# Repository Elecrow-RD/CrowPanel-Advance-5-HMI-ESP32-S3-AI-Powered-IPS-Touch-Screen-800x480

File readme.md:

## Menu
### 1, Product picture
### 2, Product version number
### 3, product information
### 4, Use the driver module
### 5,Quick Start
### 6,Folder structure.
### 7,Pin definition
### 8,Guidelines for downloading some of the files from the github repository

### 1, Product picture

### 2, Product version number

|      | Hardware | Software | Remark |
| ---- | -------- | -------- | ------ |
| 1    | V1.0     | V1.0     | old |
| 2    | V1.1     | V1.1     | old |
| 3    | V1.2     | V1.2     | old |
| 4    | V1.3     | V1.2     | latest |

### Version update points:

① **Version 1.1** updated the control of backlight on the basis of the original, the backlight of version 1.1 is controlled by STC8H1K28 microcontroller, and the backlight is lit in the program by sending the value to this microcontroller address (0x30). The values are 0x05, 0x06, 0x07, 0x08, 0x09 and 0x10, where 0x05 switches off the backlight and 0x10 is the maximum brightness.

The control of the buzzer is similar to that of the backlight: sending 0x15 activates the buzzer, while sending 0x16 deactivates it.

The speaker is controlled in the same manner: sending 0x17 activates the speaker, while sending 0x18 deactivates it.

② **Version 1.1** has a new option for function switching, see above for details. When using the case, please select the corresponding program to test or modify according to the version number of your motherboard.

③ **Version 1.2** introduces an updated backlight control function. In this iteration, the backlight is managed by the STC8H1K28 microcontroller. The programme illuminates the backlight by transmitting numerical values to the microcontroller's address (0x30). Brightness adjustment spans 0-245 levels, where 0 denotes maximum brightness, 244 represents minimum brightness, and 245 disables the backlight.
Updated the button module.
The buzzer control principle mirrors that of the backlight: sending 246 activates the buzzer, while sending 247 deactivates it.

④ **Version 1.2** ,Only the button component has been updated. All other hardware and I/O pins remain the same as in the previous version.

⑤ **Version 1.3** is simply an update to the previous version that modifies the packaging of the touchscreen FPC connector. There are no other differences.

### 3, product information

| Main Chip-ESP32-S3-WROOM-1-N16R8         |                                                              |
| -------------------------------------------- | ------------------------------------------------------------ |
| CPU/SoC                                      | high-performance Xtensa 32-bit LX7 dual-core processor, with up to 240MHz |
| System Memory                                | 512KB SRAM、8M PSRAM                                         |
| Memory                                       | 16M Flash，384KB ROM                                         |
| Development Language                         | MicroPython、C/C++                                           |
| Development Environment                      | ESP-IDF、Arduino IDE、PlatformIO、MicroPython        |
| **Screen**                                   |                                                              |
| Size                                         | 5.0 inch                                                     |
| Diver IC                                     | ST7262                                                       |
| Resolution                                   | 800*480                                                      |
| Display Panel                                | IPS Panel                                                    |
| Touch Panel                                  | Capacitive Single Touch                                      |
| Viewing Angle                                | 178°                                                         |
| Brightness                                   | 400 cd/m²(Typ.)                                              |
| Color Depth                                  | 16-bit                                                       |
| **Wireless Communication - Onboard Antenna** |                                                              |
| WiFi                                         | Support 2.4GHz, 802.11a/b/g/n                                |
| Bluetooth                                    | Support Bluetooth 5.0 and BLE                                |
| Other                                        | **Zigbee、LoRa、nRF2401、Matter、Thread and Wi-Fi 6 (Optional)** |
| **Interface/Function**                       |                                                              |
| Interface                                    | USB port, UART, I2C, SD card slot, battery socket, speaker port, microphone, etc. |
| Function                                     | RTC clock, audio amplifier, volume control, battery charge management, USB to UART, etc. |
| **Button/LED Indicator**                     |                                                              |
| Reset Button                                 | Yes, press to reset device                                   |
| Boot Button                                  | Yes, press and hold the power button to burn the program     |
| PWR                                          | Power indicator                                              |
| CHG                                          | Lithium battery charging status, completion indication       |
| **Other**                                    |                                                              |
| Installation method                          | Back hanging, fixed hole                                     |
| Operating temperature                        | -20~70 °C                                                    |
| Storage temperature                          | -30~80 °C                                                    |
| Power Input                                  | 5V/2A, USB or UART terminal                                  |
| Active Area                                  | 108mm*65mm                                                   |
| Dimensions                                   | 136.4\*84.7*15.4mm                                            |

### 4, Use the driver module

| Name   | dependency library                      |
| ------ | --------------------------------------- |
| LVGL   | lvgl/lvgl@8.3.3                         |
| ST7789 | Adafruit GFX Library<br/>version=1.11.0 |

### 5,Quick Start
### Arduino IDE starts

#### Teaching Case Path：./example/example_code5.0

1.Download the library files used by this product to the 'libraries' folder.

C:\Users\Documents\Arduino\libraries\

2.Open the Arduino IDE

3.Open the code configuration environment and burn it

### ESP-IDF starts

#### Teaching Case Path：./example/idf_code

1.Right-click on an empty space in the project folder and select "Open with VS Code" to open the project.

2.In the IDF plug-in, select the port, then compile and flash

### 6,Folder structure.

|--3D file： Contains 3D model files (.stp) for the hardware. These files can be used for visualization, enclosure design, or integration into CAD software.

|--Datasheet: Includes datasheets for components used in the project, providing detailed specifications, electrical characteristics, and pin configurations.

|--Eagle_SCH&PCB: Contains **Eagle CAD** schematic (`.sch`) and PCB layout (`.brd`) files. These are used for circuit design and PCB manufacturing.

|--example: Provides example code and projects to demonstrate how to use the hardware and libraries. These examples help users get started quickly.

|--factory_firmware: Stores pre-compiled factory firmware that can be directly flashed onto the device. This ensures the device runs the default functionality.

|--factory_sourcecode:  Contains the source code for the factory firmware, allowing users to modify and rebuild the firmware as needed.

|--libraries: Includes necessary libraries required for compiling and running the project. These libraries provide drivers and additional functionalities for the hardware.

|--Squareline_studio Instructions for use: Squareline_studio instructions: Demonstrate the use of squareline studio.

### 7,Pin definition

#define HSPI_MISO  4

#define HSPI_MOSI  6

#define HSPI_SCLK  5

#define HSPI_SS    19

#define SD_MOSI 6

#define SD_MISO 4
#define SD_SCK 5

#define SD_CS 0 //The chip selector pin is not connected to IO

#define I2S_DOUT 4

#define I2S_BCLK 5

#define I2S_LRC 6

​      cfg.pin_d0 = GPIO_NUM_21;    // B0

​      cfg.pin_d1 = GPIO_NUM_47;    // B1

​      cfg.pin_d2 = GPIO_NUM_48;   // B2

​      cfg.pin_d3 = GPIO_NUM_45;    // B3

​      cfg.pin_d4 = GPIO_NUM_38;    // B4

​      cfg.pin_d5 = GPIO_NUM_9;    // G0

​      cfg.pin_d6 = GPIO_NUM_10;    // G1

​      cfg.pin_d7 = GPIO_NUM_11;    // G2

​      cfg.pin_d8 = GPIO_NUM_12;   // G3

​      cfg.pin_d9 = GPIO_NUM_13;   // G4

​      cfg.pin_d10 = GPIO_NUM_14;   // G5

​      cfg.pin_d11 = GPIO_NUM_7;  // R0

​      cfg.pin_d12 = GPIO_NUM_17;  // R1

​      cfg.pin_d13 = GPIO_NUM_18;  // R2

​      cfg.pin_d14 = GPIO_NUM_3;  // R3

​      cfg.pin_d15 = GPIO_NUM_46;  // R4

      cfg.pin_henable = GPIO_NUM_42;
      
      cfg.pin_vsync = GPIO_NUM_41;
      
      cfg.pin_hsync = GPIO_NUM_40;
      
      cfg.pin_pclk = GPIO_NUM_39;

​     cfg.pin_sda = GPIO_NUM_15;

​      cfg.pin_scl = GPIO_NUM_16;

### 8,Guidelines for downloading some of the files from the github repository

##### 1, open the link in your browser: https://downgit.github.io/

##### 2, paste the URL of the GitHub destination folder in the input box (example format: `https://github.com/username/repository name/tree/branch name/folder path`)

##### 3, even a that way to download the file.

①Click the “Create Download Link” button to create a download link, copy the link and open it with your browser to download the contents of the corresponding folder directly.

②Click Download, and you can also download it directly.

#### Note: DownGit downloads are stored by default in **your browser's default downloads folder**, usually:

- **Windows**: `C:\Users\your username\Downloads\` (downloads folder)
- **macOS**: `~/Downloads/` (downloads folder)
- **Linux**: `~/Downloads/` (Downloads folder)

If you change the default download path in your browser, the file will be stored in the download location you set. You can find the downloaded file path in your browser's **Download History** (shortcut `Ctrl + J` or `Cmd + J`).

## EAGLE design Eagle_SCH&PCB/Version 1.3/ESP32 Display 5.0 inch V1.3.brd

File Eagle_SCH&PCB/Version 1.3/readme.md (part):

# 5.0-Inch ESP32-S3 Hardware Driver Guide

| Item | Details |
|---|---|
| Document Version | V1.0 |
| Applicable Hardware | ESP32 Display 5.0 inch V1.3 |
| Baseline Date | 2026-07-30 |
| Author | OpenAI Codex (compiled through cross-referencing project materials) |
| Purpose | Hardware maintenance, driver porting, production testing, and onboarding handoff |

## 1. Document Scope and Determination Criteria

This document is based on cross-verification of the following project materials:

1. `Version 1.3/ESP32 Display 5.0 inch V1.3.sch`: EAGLE 9.6.2 schematic source file, used as the primary hardware evidence for components and net connections.
2. `Version 1.3/ESP32 Display 5.0 inch V1.3.brd`: PCB netlist, used to verify schematic nets and component pad connections.
3. `Version 1.3/ESP32 Display 5.0 inch V1.3.pdf`: Single-page schematic, used for visual verification of functional sections, interface names, and component models.
4. Board-level examples under `Arduino/`: Used as the project’s verified driver baseline, primarily covering display/touch, TF card, I2S audio, DHT20, nRF24L01, SX1262 LoRaWAN, and UART/Zigbee examples.

Conflicts are resolved according to the following priority:

> Working code configurations in successfully tested examples > actual PCB nets > schematic nets/labels > comments and filenames.

However, obvious placeholder values, conflicting comments, or parameters that do not correspond to actual electrical connections in the code are not automatically treated as reliable hardware facts. Such items are identified separately as risks in this document.

### 1.1 Evidence Levels

| Level | Meaning |
|---|---|
| A | The schematic/PCB matches the project driver code, and the code performs actual initialization or read/write operations |
| B | The schematic/PCB has been confirmed, but the project has no corresponding ESP32 driver, or the function is managed only by the onboard control MCU |
| C | The project provides a driver example, but it targets an optional module connected through an interface rather than a permanently mounted motherboard component |
| D | Only the presence of hardware or reserved signals can be confirmed; key protocols or parameters are missing and must be tested before porting |

No build logs, test reports, or test result files were found in the repository. Therefore, “verified code” in this document refers specifically to the product example baseline provided by the repository and does not mean that all tests were rerun on physical hardware for this review.

## 2. Product Hardware Architecture

The main controller is an ESP32-S3-WROOM-1-N16R8. The display uses an 800 × 480 RGB565 parallel interface. The GT911, onboard STC8H1K28 control MCU, RTC, and external I2C interface share GPIO15/16. GPIO4/5/6 and GPIO19/20 are multiplexed among the TF card, I2S, digital microphone, and wireless expansion interface through two CH486F analog switches and DIP-switch selection.

The onboard STC8H1K28 is an important auxiliary controller. It connects to touch reset, LCD backlight enable/power, the buzzer, charging status indicators, and ESP32_EN, and provides a board-control command interface to the ESP32 at I2C address `0x30`. Do not mistake these functions for direct ESP32 GPIO control.

## 3. Peripheral Overview

| Category | Component/Function | Primary Interface | ESP32 Resources | Onboard/External | Evidence |
|---|---|---|---|---|---|
| MCU | ESP32-S3-WROOM-1-N16R8 | Main controller | All board-level resources | Onboard | A |
| Auxiliary MCU | STC8H1K28-36I-LQFP32 | I2C board control | SDA15, SCL16; recovery pin GPIO1 indirectly associated with TP_INT | Onboard | A/B |
| Display | 5.0-inch 800×480 IPS RGB display | RGB565 parallel interface | GPIO3/7/9-14/17/18/21/38/45-48, 39-42 | Onboard | A |
| Touch | GT911 capacitive touch | I2C | SDA15, SCL16, INT GPIO1; RST controlled by STC | Onboard | A |
| Storage | MicroSD/TF card | SPI | MISO4, SCK5, MOSI6; see risk notes for CS | Onboard | A/discrepancy |
| RTC | PCF8563-compatible device | I2C | SDA15, SCL16, 32.768 kHz crystal, CR1220 backup | Onboard | B |
| Audio Output | NS4168 amplifier + speaker interface | I2S | DOUT4, BCLK5, LRCLK6; amplifier enabled by STC command | Onboard | A |
| Audio Input | LMD3526B261 digital MEMS microphone | I2S/PDM-type digital interface | CLK19, DATA20 | Onboard | B |
| Buzzer | BEEP_5025 passive buzzer | STC GPIO/PWM | No direct ESP32 connection; STC `P2.7/BEEP` | Onboard | B |
| Temperature and Humidity | DHT20 | I2C | SDA15, SCL16 | External | C |
| 2.4 GHz | nRF24L01 | SPI + CE | MISO4, SCK5, MOSI6, CSN19, CE20 | External | C |
| LoRa | SX1262 | SPI + DIO/RESET/BUSY | MISO4, SCK5, MOSI6, NSS8, DIO1 20, RESET19, BUSY2 | External | C |
| Zigbee/Serial Module | Model not specified | UART | RX19, TX20, 115200 8N1 | External | C/D |
| USB-to-Serial | CH340K | USB 2.0/UART0 | ESP_TXD0/ESP_RXD0, automatic download circuit | Onboard | B |
| Native USB | USB-C D+/D- | USB 2.0 | ESP32-S3 native USB fixed pins (nets routed through resistors) | Onboard | B |
| Power Input | USB-C 5 V, external 5 V/VIN | Power | Not GPIO | Onboard | B |
| Battery Charging | TP4059 + CR1220 RTC backup battery interface | Analog power/status | Status monitored by STC | Onboard | B |
| Main-Power DC/DC | RY3420/HM3416H | Step-down conversion | Not GPIO | Onboard | B |
| LCD Backlight | MT9201 | Boost constant-current + STC control | Indirectly controlled by ESP32 through I2C `0x30` | Onboard | A |
| Power/Charging LEDs | Red/green LEDs | STC GPIO | No direct ESP32 connection | Onboard | B |
| Buttons | BOOT, RESET | GPIO0, ESP32_EN | Active low | Onboard | B |
| DIP Switch | K1/DSHP02TS-S | Multiplexing selection | SEL0, SEL1, hardware configuration | Onboard | A/B |
| Expansion Interfaces | UART, I2C, GPIO, I2S/wireless headers | Multiple protocols | GPIO2/4/5/6/8/15/16/19/20, etc. | Onboard connectors | B/C |

## 4. ESP32-S3 GPIO Summary

| GPIO | Actual Project Function | Direction/Electrical Mode | Multiplexing and Restrictions |
|---:|---|---|---|
| 0 | BOOT; CS parameter passed by the SD example | Boot strapping pin, button active low | Peripherals should not pull it low during reset; see 6.4 regarding the validity of SD_CS |
| 1 | `IO1_TP_INT`, touch-interrupt net; examples use a low pulse to recover board control/touch | Normally input; open-drain-equivalent operation during fault recovery: output low for 120 ms, then return to input | Must not be continuously driven high in push-pull mode; code does not enable GT911 interrupt polling |
| 2 | Wireless expansion CS; SX1262 BUSY | Digital I/O | LoRa example uses it for BUSY; associated with J11 expansion functions |
| 3 | LCD R6 net, corresponding to one RGB565 red data bit | High-speed push-pull output | Dedicated to LCD |
| 4 | SPI MISO / I2S DOUT / wireless MISO | Input or push-pull output, depending on mode | Multiplexed through CH486F; functions are mutually exclusive |
| 5 | SPI SCK / I2S BCLK / wireless SCK | Push-pull clock output | Multiplexed through CH486F; functions are mutually exclusive |
| 6 | SPI MOSI / I2S LRCLK / wireless MOSI | Push-pull output | Multiplexed through CH486F; functions are mutually exclusive |
| 7 | LCD R3 | High-speed push-pull output | Dedicated to LCD |
| 8 | Wireless BUSY/expansion; SX1262 NSS | Digital I/O | LoRa code uses it as a push-pull chip select; verify DIP-switch and connector settings |
| 9-14 | LCD G2-G7 | High-speed push-pull output | Dedicated to LCD |
| 15 | I2C SDA | Bidirectional open-drain, with onboard 4.7 kΩ pull-up to 3.3 V | Shared by GT911, STC, RTC, and external I2C |
| 16 | I2C SCL | Open-drain clock, with onboard 4.7 kΩ pull-up to 3.3 V | Same as above |
| 17, 18 | LCD R4, R5 | High-speed push-pull output | Dedicated to LCD |
| 19 | nRF24 CSN / SX1262 RESET / UART RX / MIC CLK / LED example | Input or output, depending on use case | Multiplexed through CH486F; multiple examples cannot run simultaneously |
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
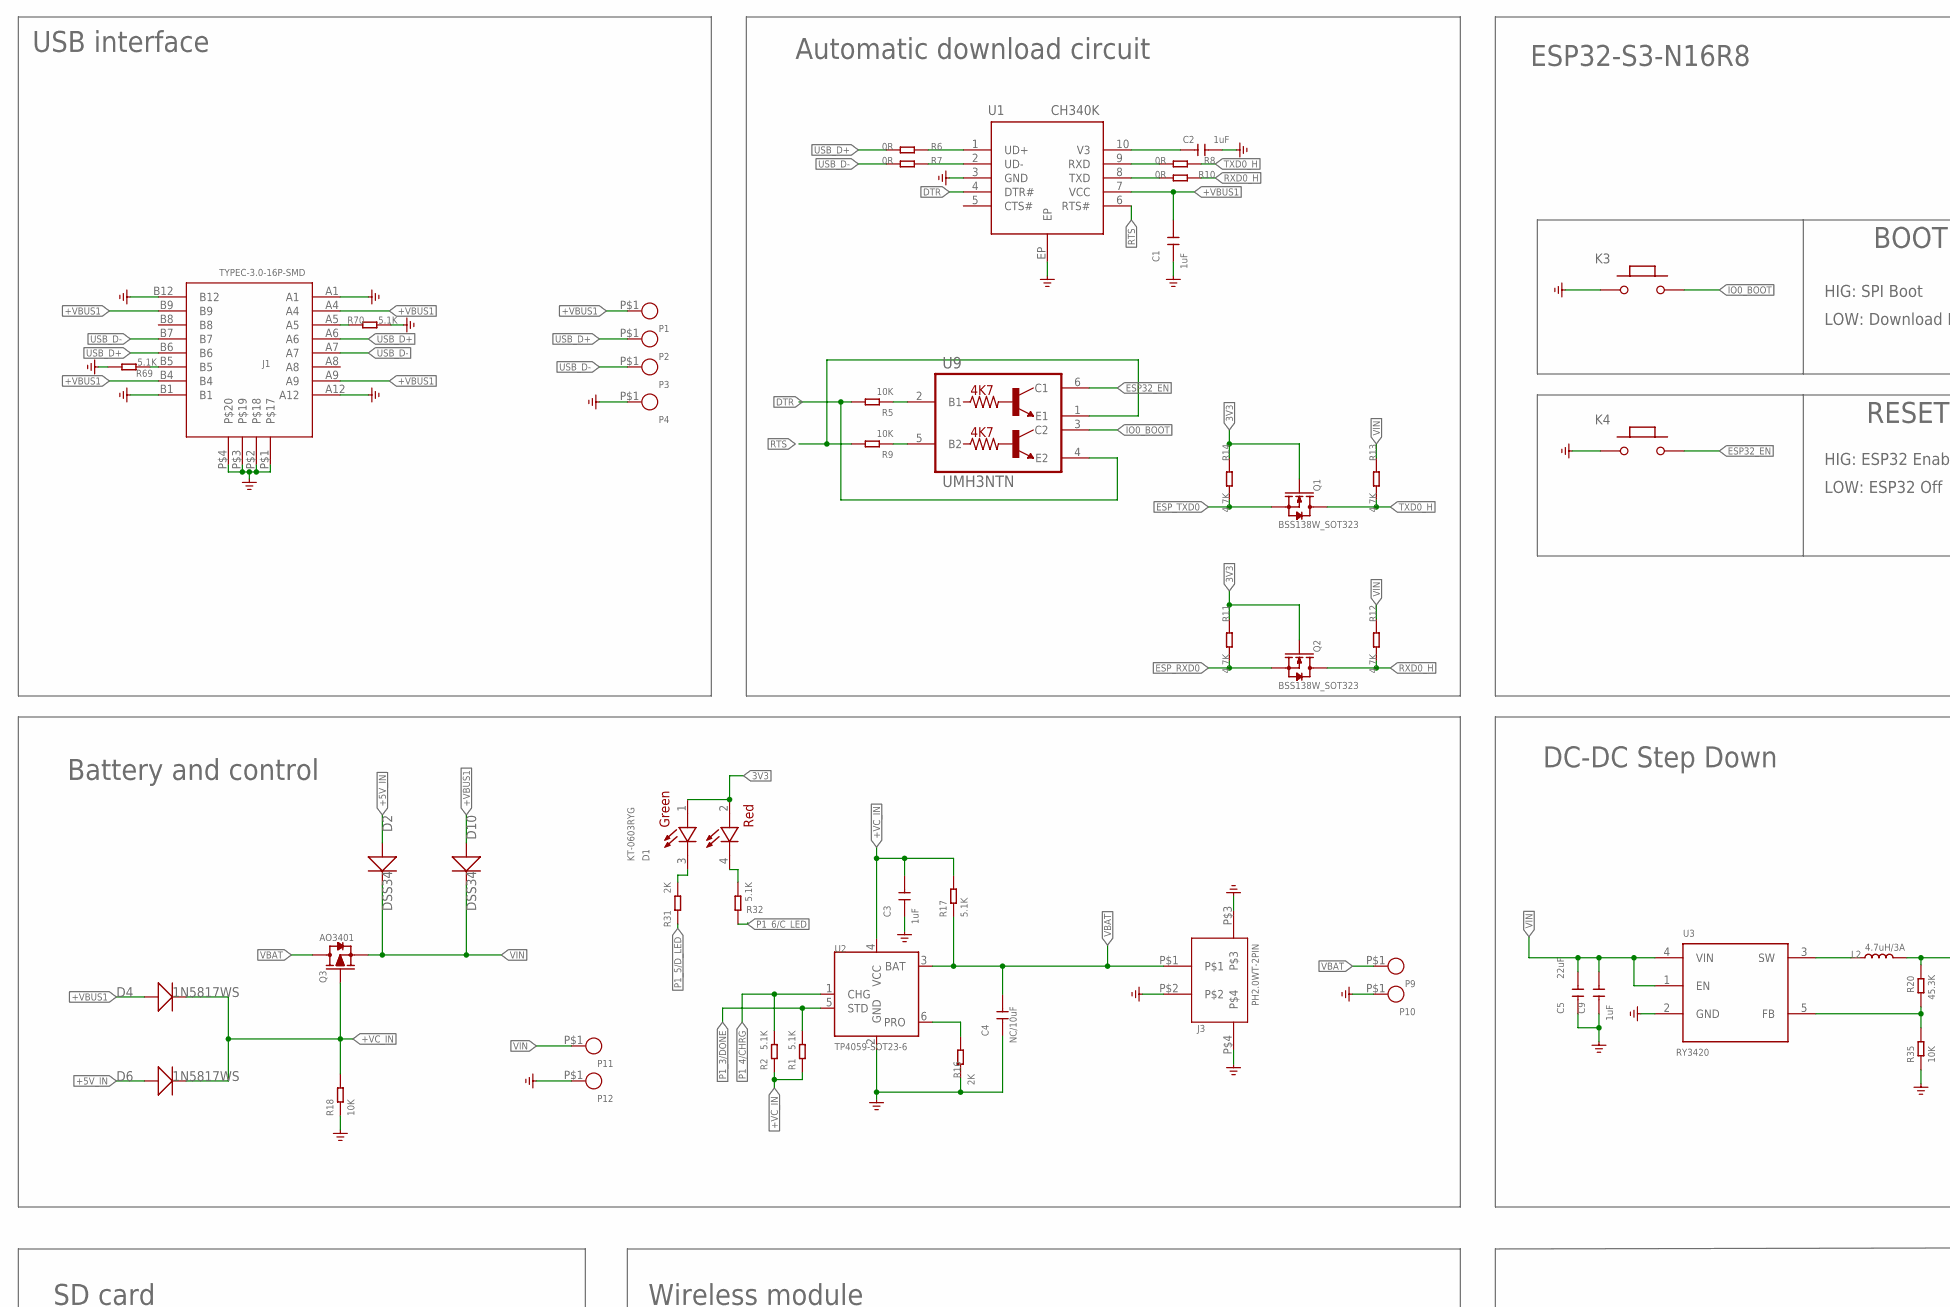
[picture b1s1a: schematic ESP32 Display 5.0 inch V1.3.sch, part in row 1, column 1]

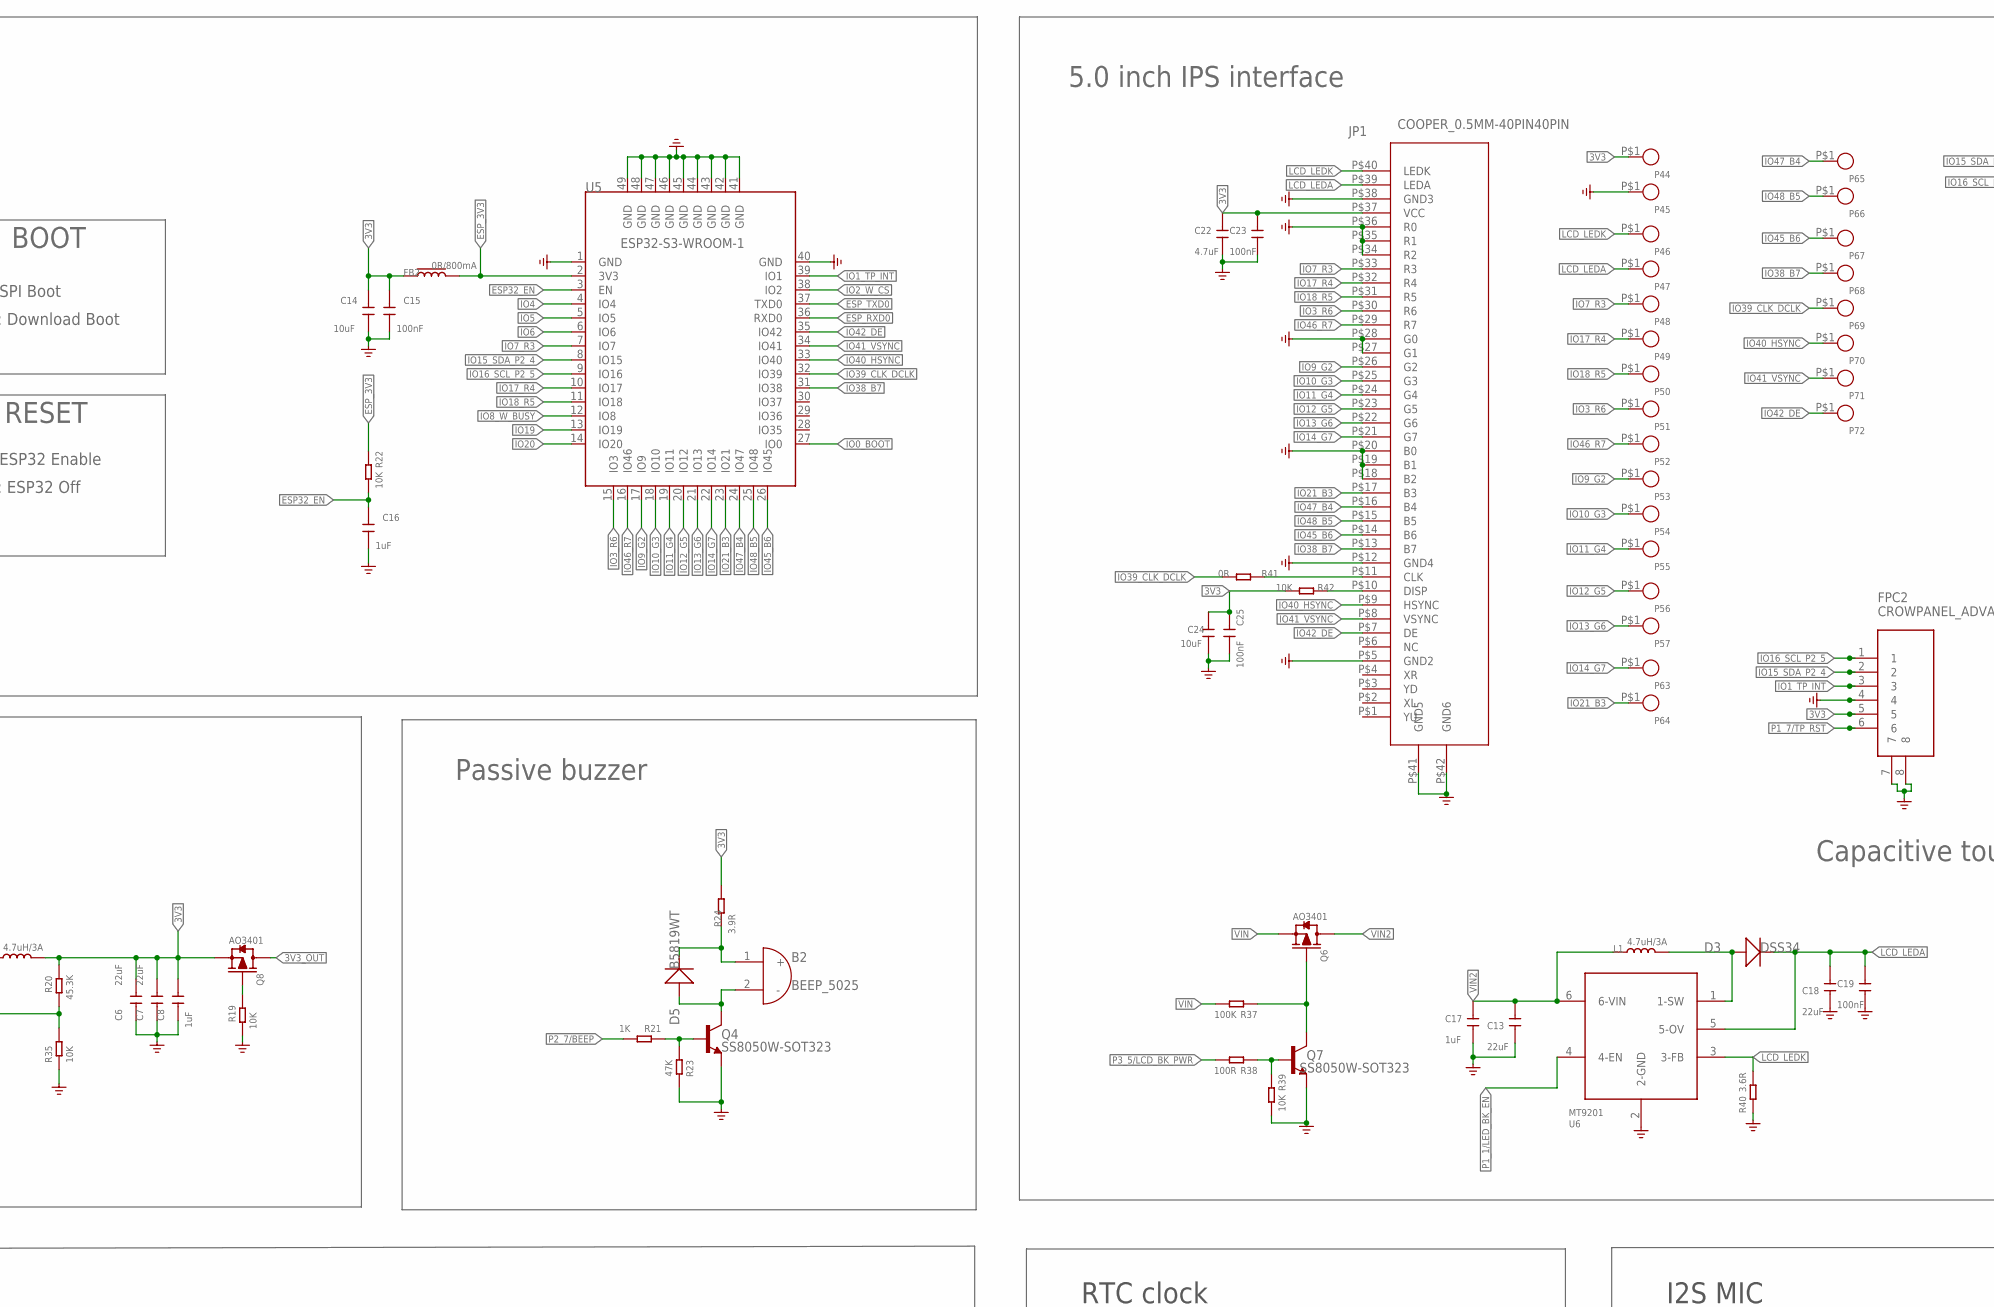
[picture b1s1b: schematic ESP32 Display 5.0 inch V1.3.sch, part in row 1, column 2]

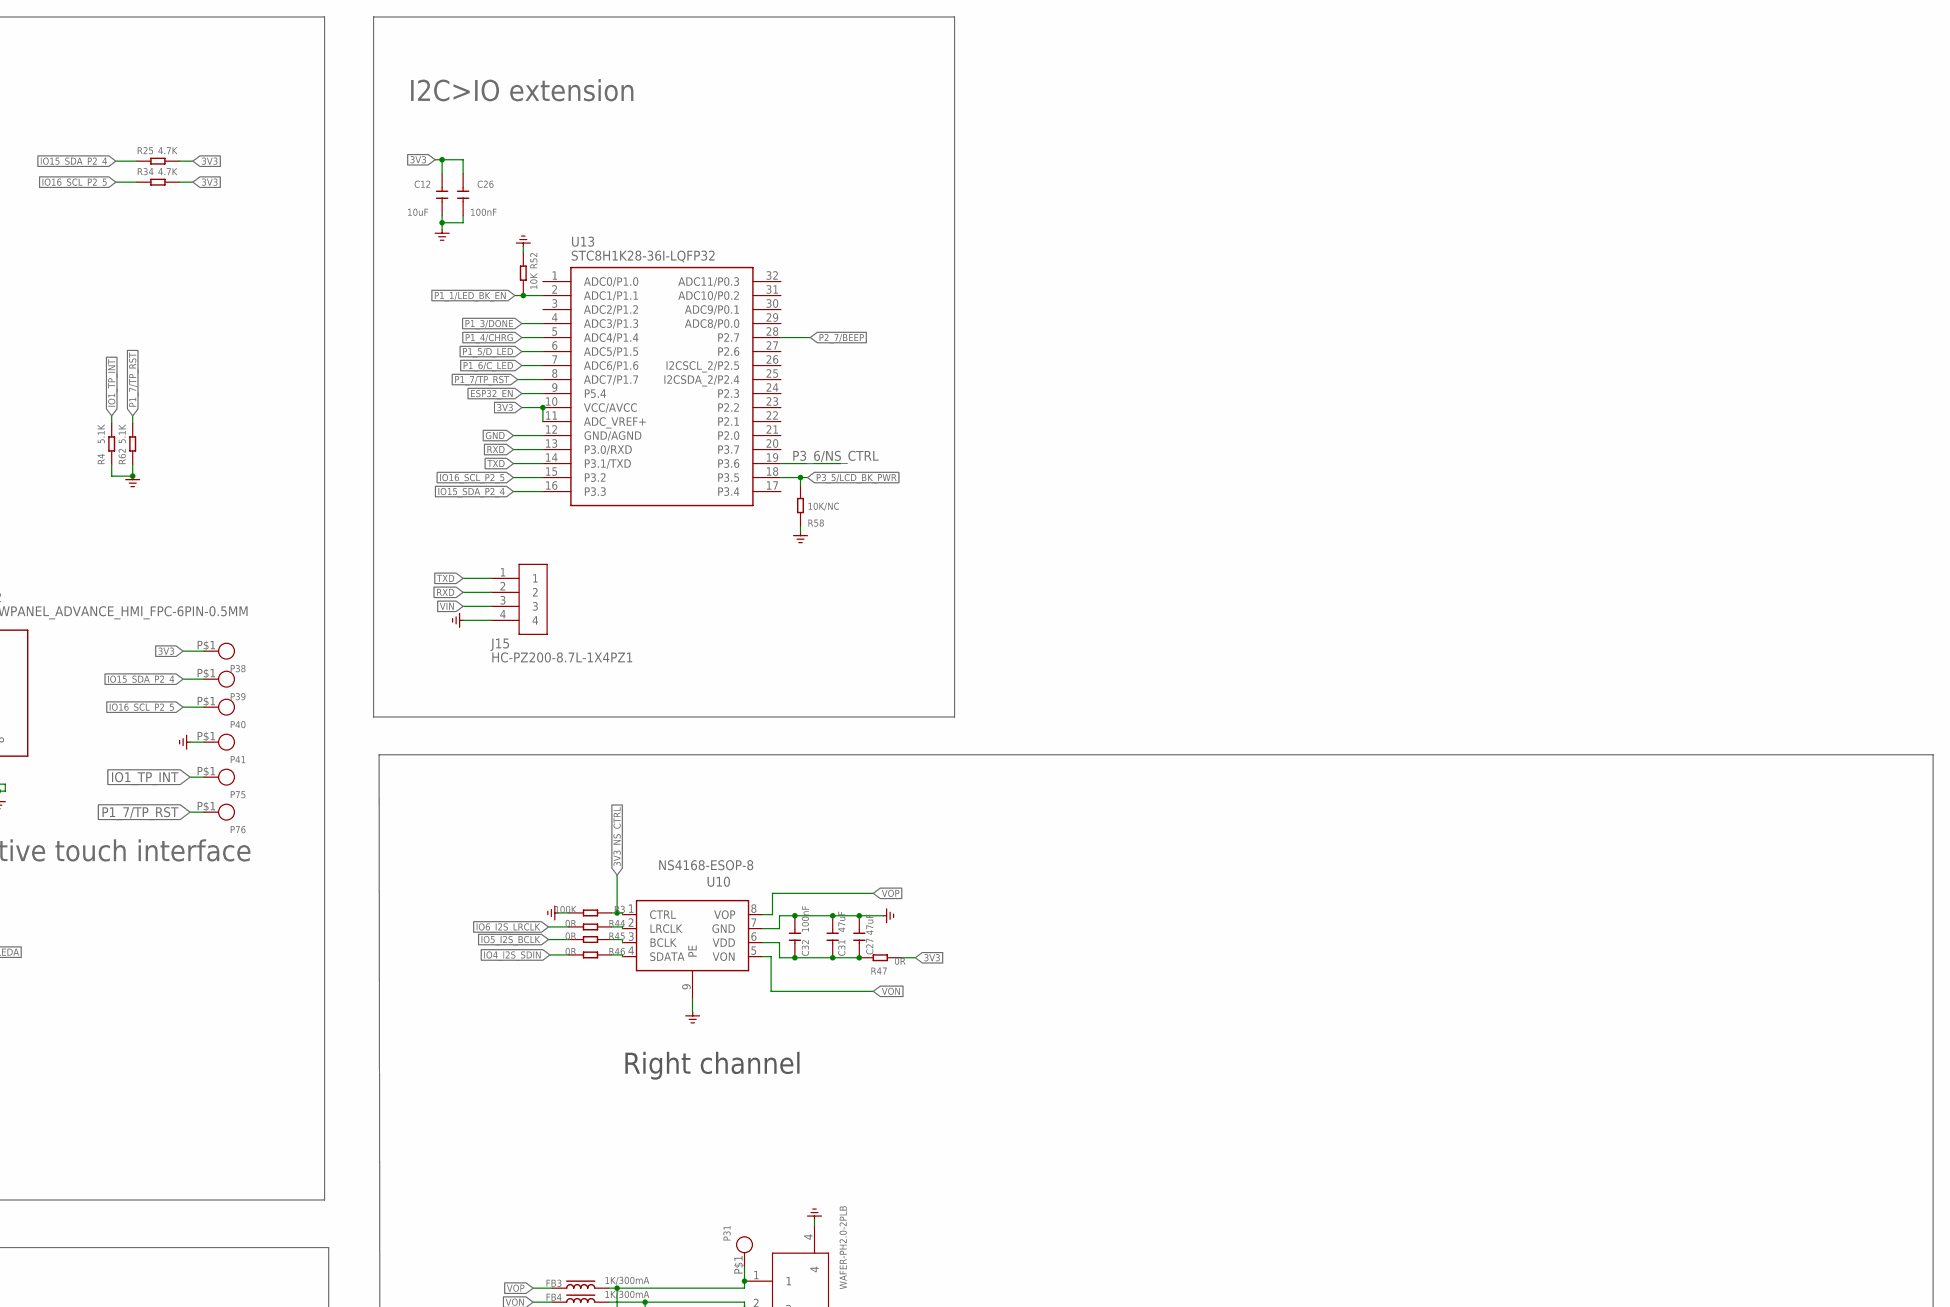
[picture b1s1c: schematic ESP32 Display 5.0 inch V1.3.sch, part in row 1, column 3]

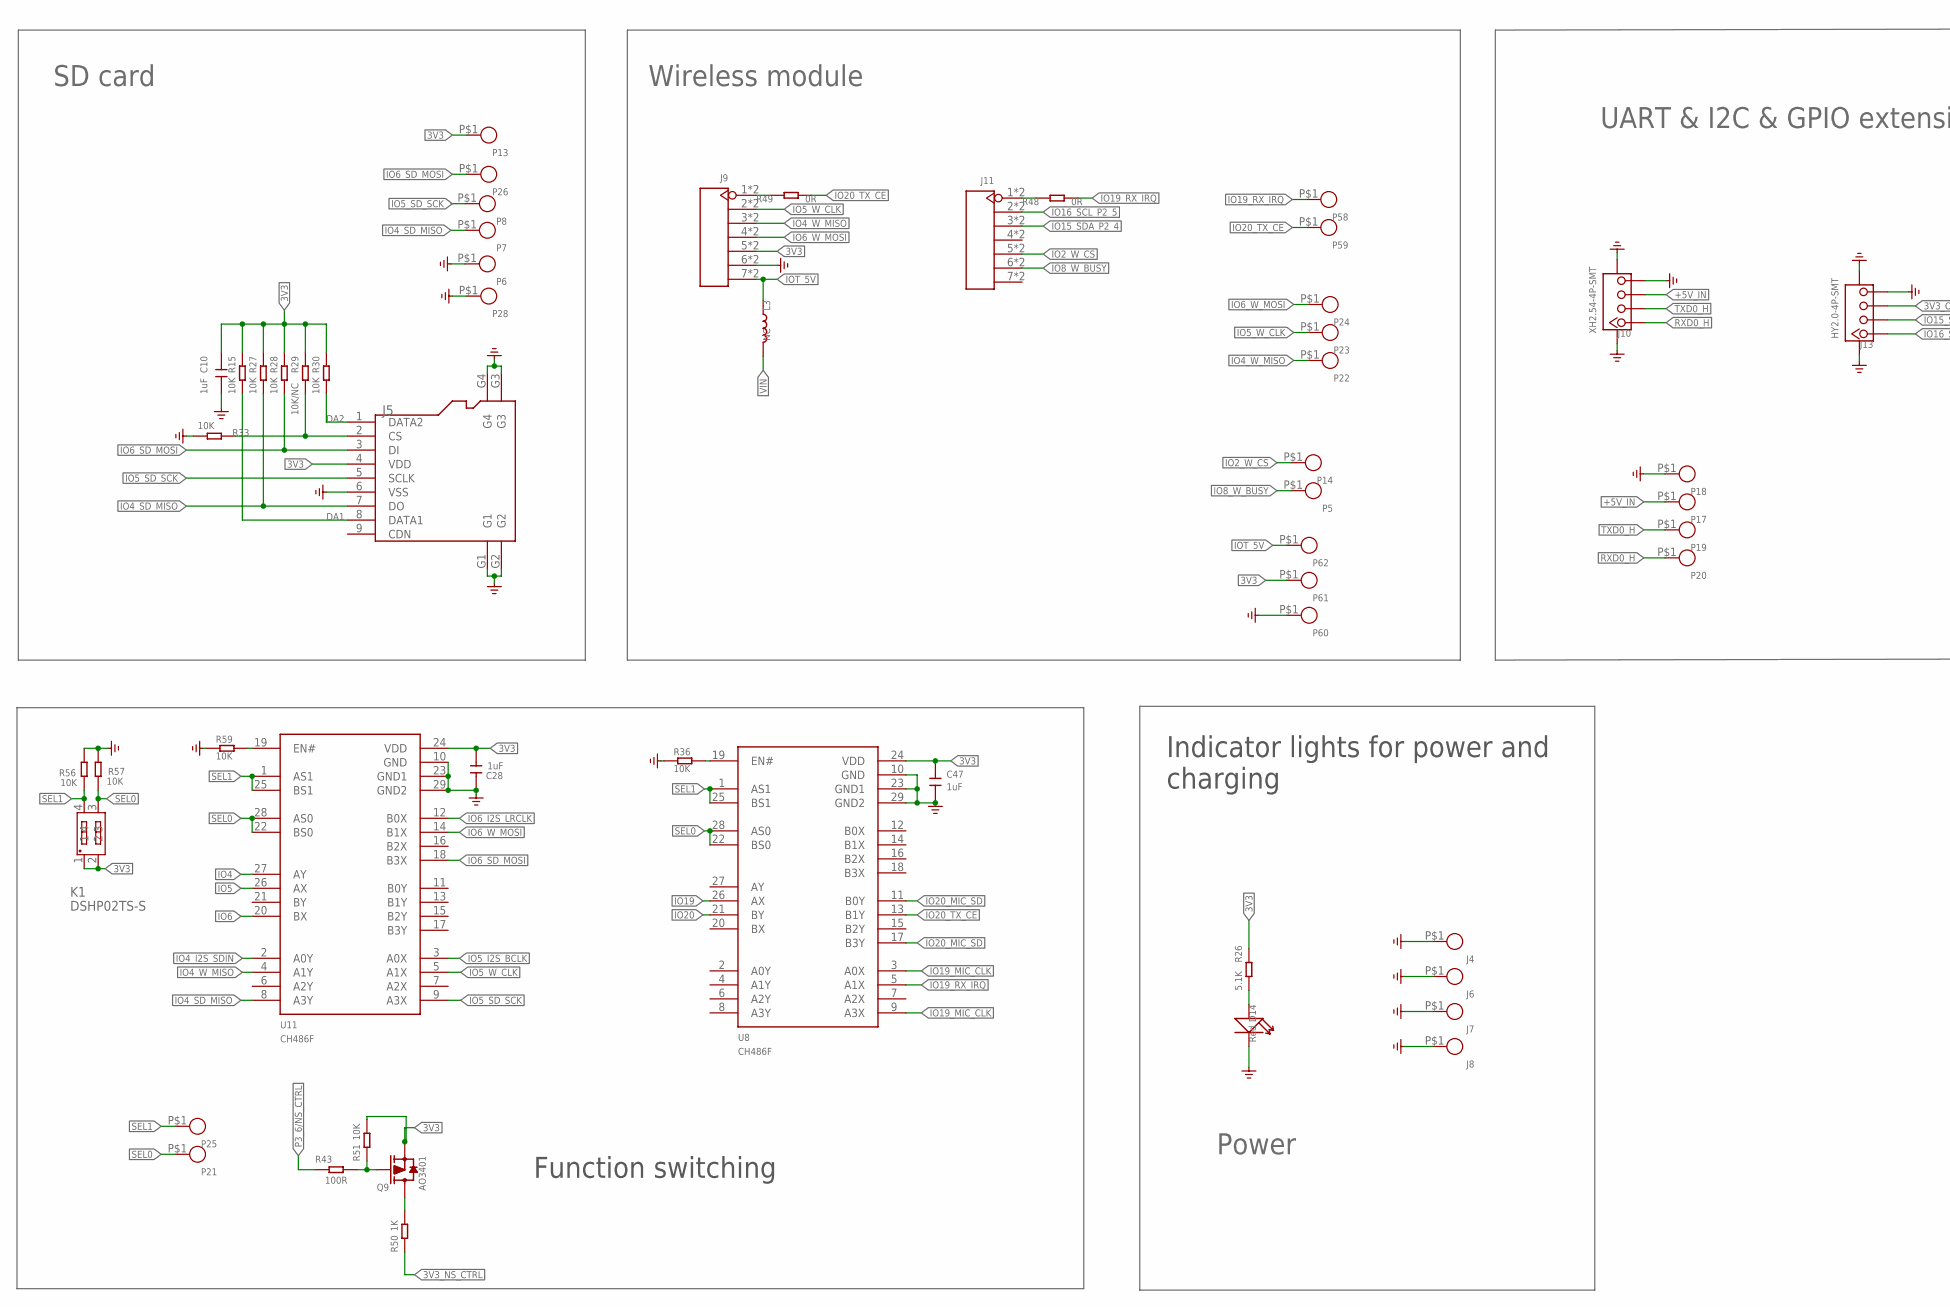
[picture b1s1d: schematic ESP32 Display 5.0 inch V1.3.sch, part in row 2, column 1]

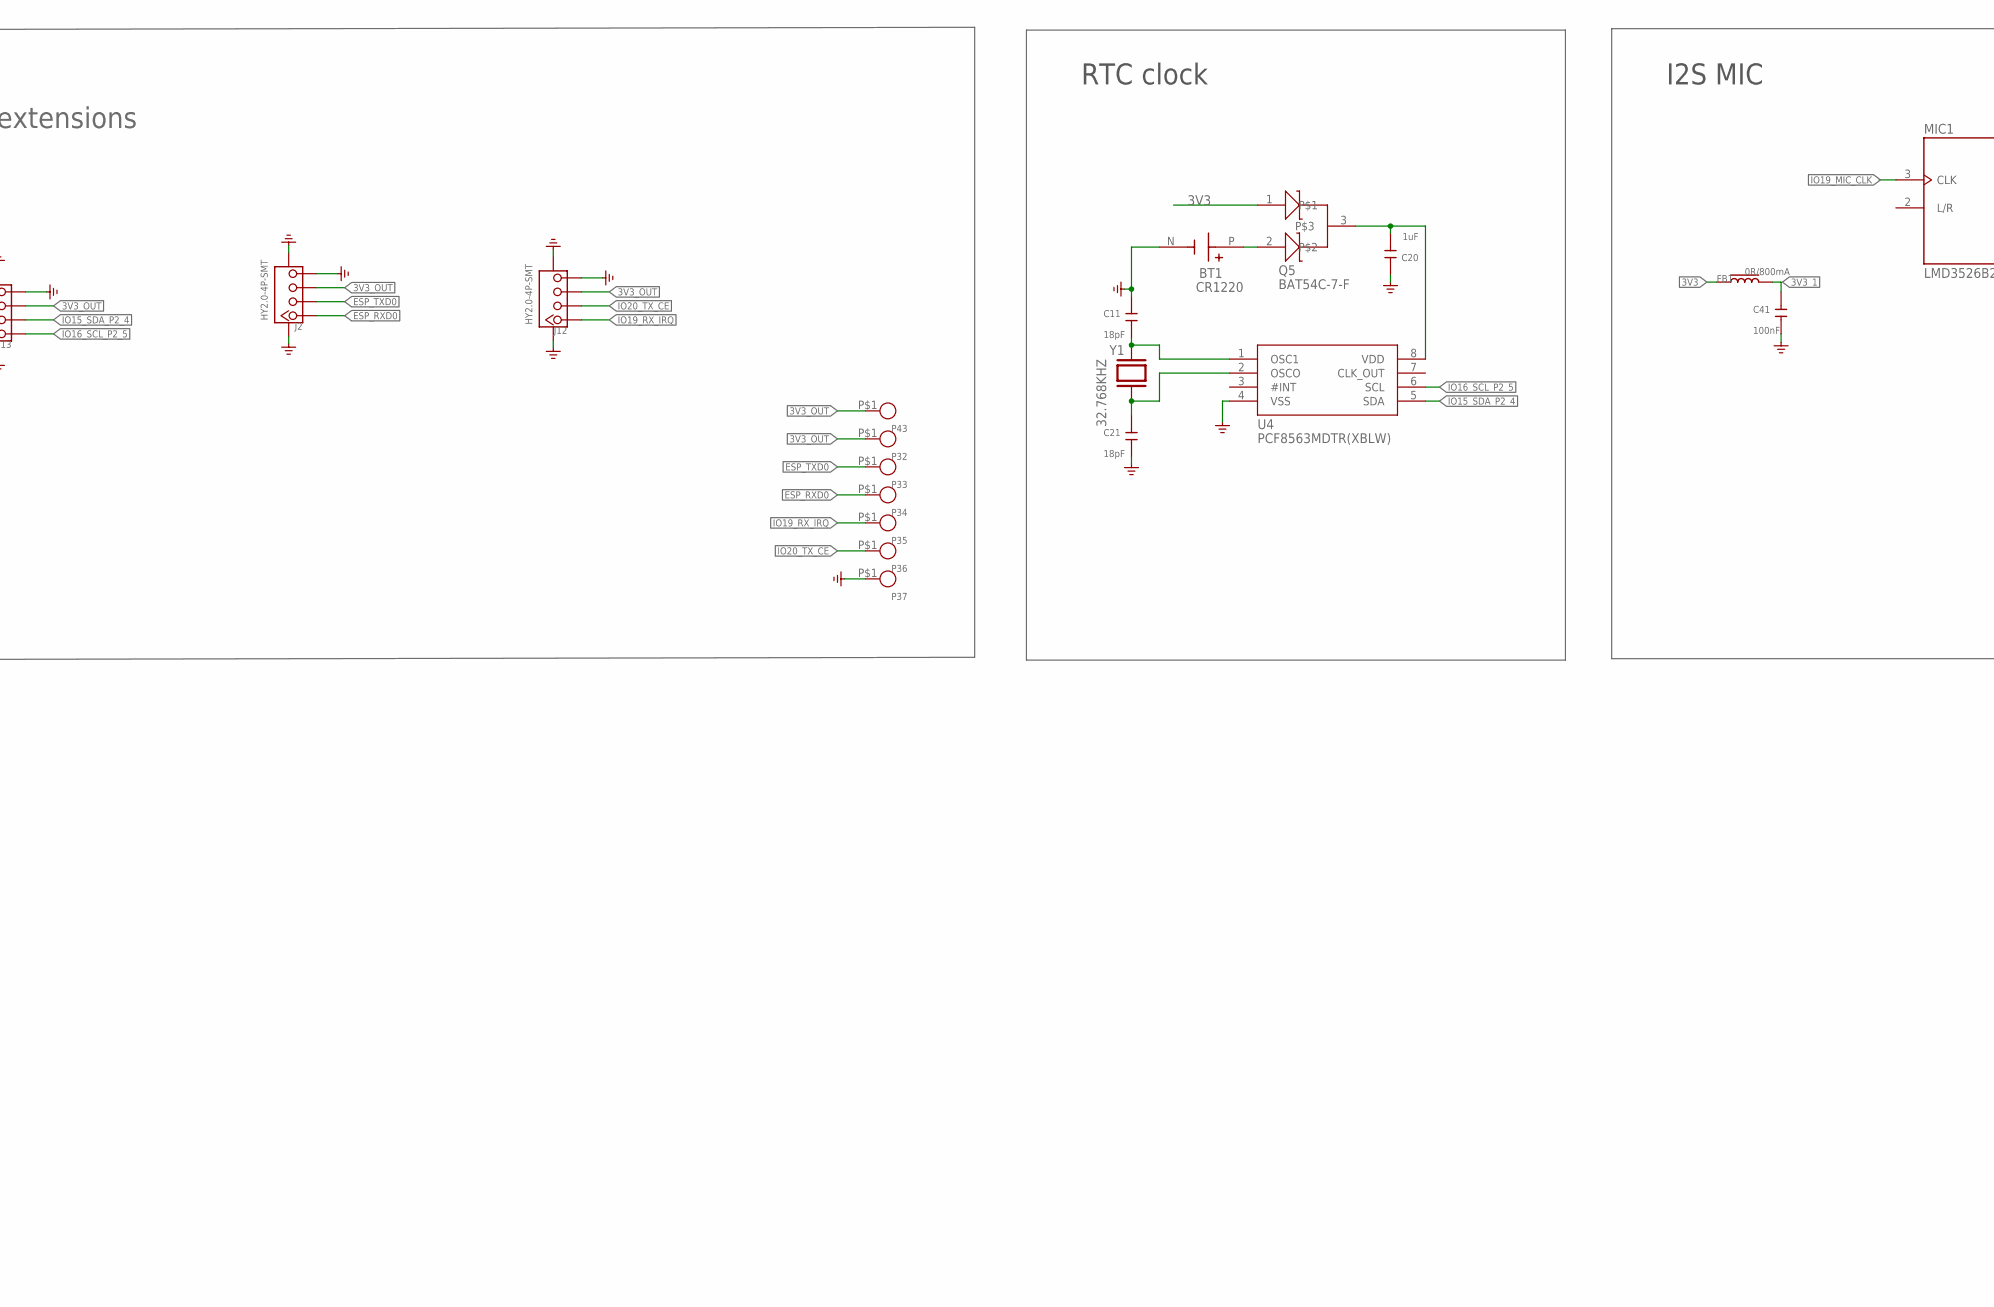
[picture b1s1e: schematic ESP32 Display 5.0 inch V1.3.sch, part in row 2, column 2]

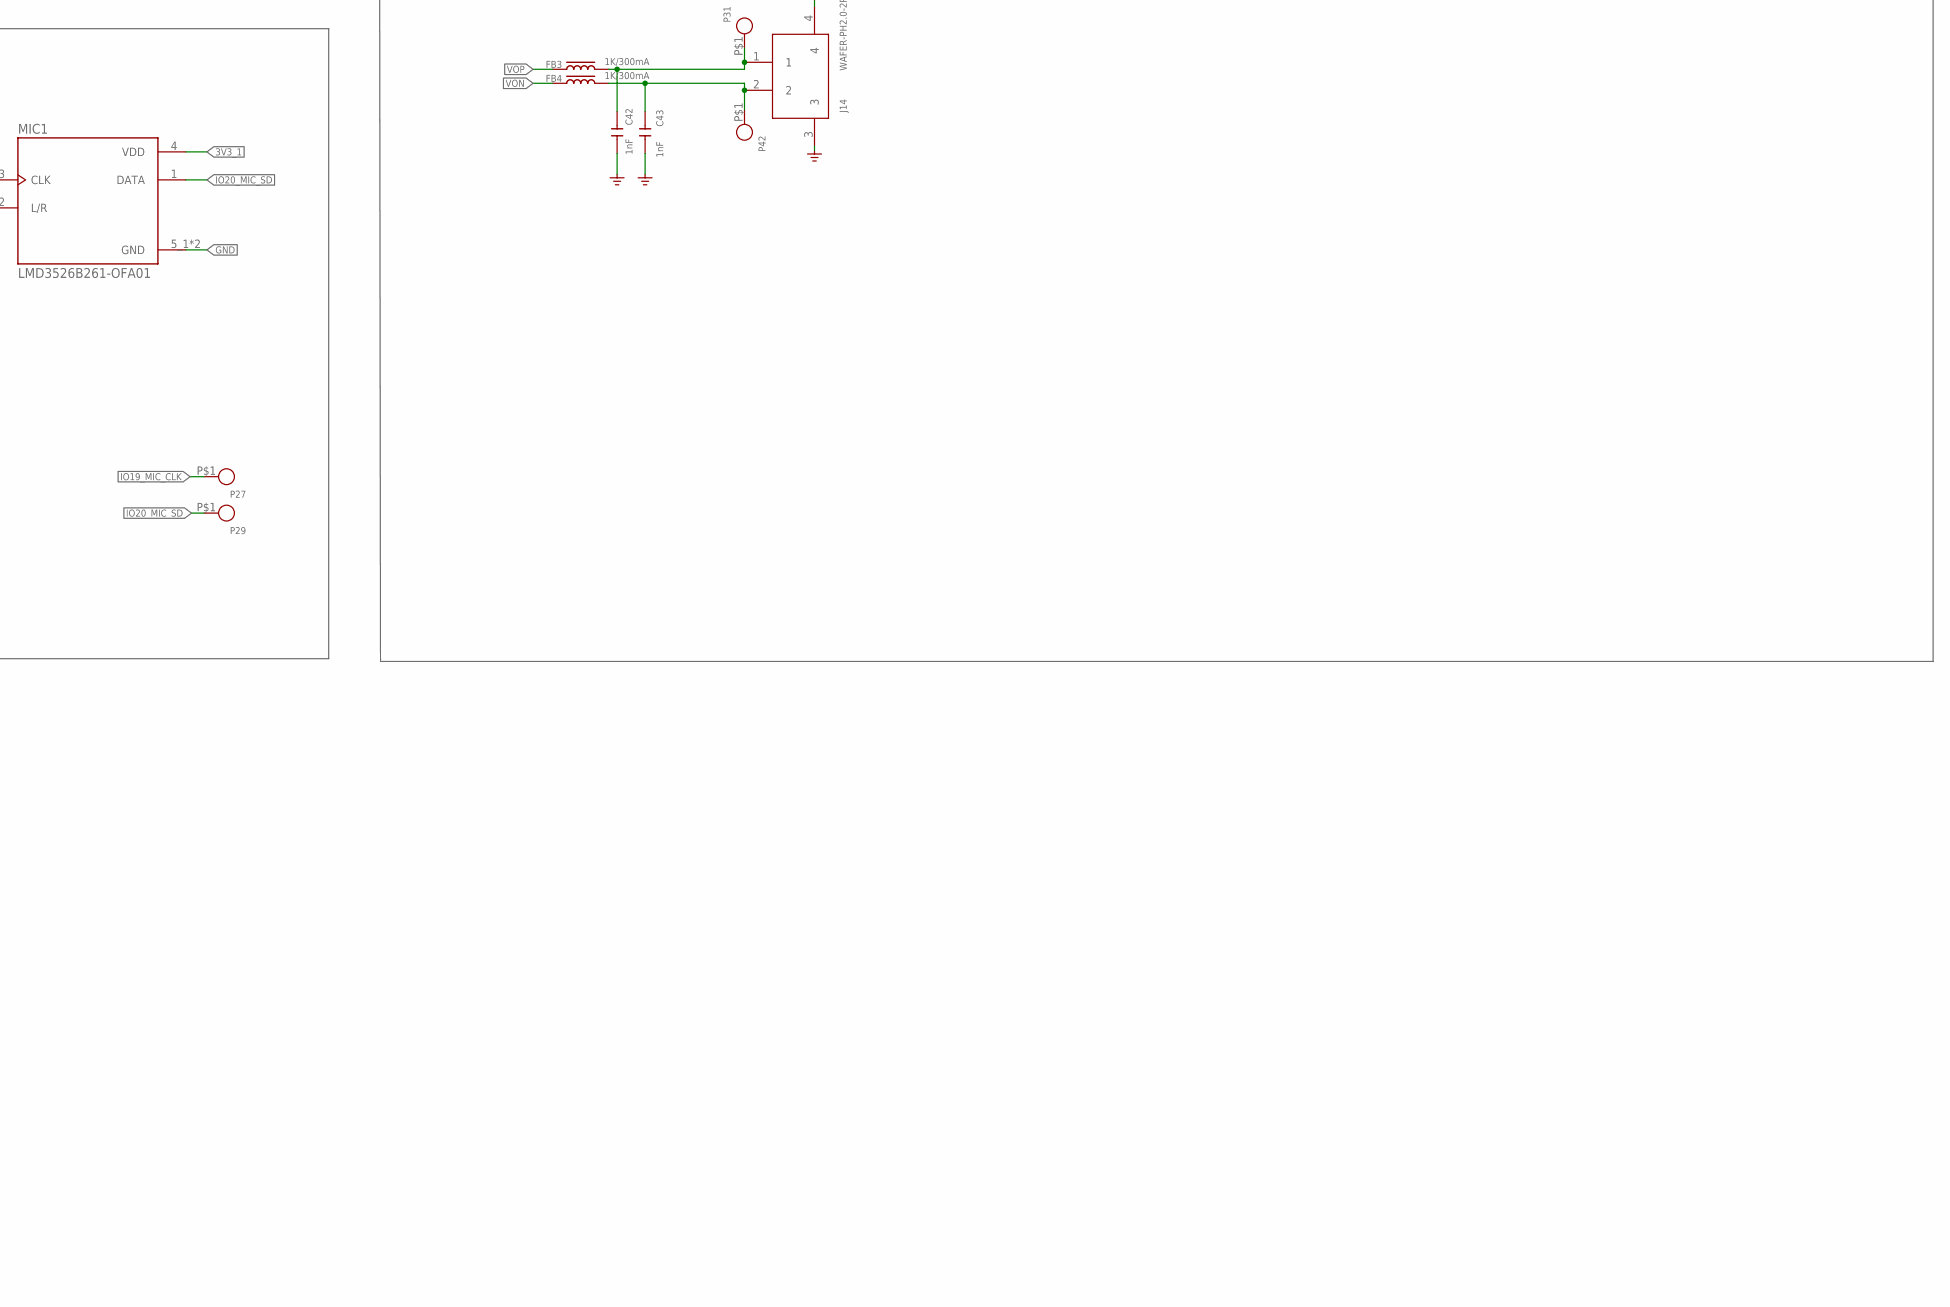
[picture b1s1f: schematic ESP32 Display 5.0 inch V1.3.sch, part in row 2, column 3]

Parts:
B2: BEEP_5025
BT1: CR1220
C1, C2, C3, C8, C9, C10, C16, C17, C20, C28, C47: 1uF; C0603
C4: NC/10uF; C0603
C5, C6, C7, C13, C18: 22uF; C0805
C11, C21: 18pF; C0603
C12, C14, C24: 10uF; C0603
C15, C19, C23, C25, C26, C32, C41: 100nF; C0603
C22: 4.7uF; C0603
C27, C31: 47uF; C0805
C42, C43: 1nF; C0603
D1: KT-0603RYG; LED_KT-0603RYG
D2, D3, D10: DSS34; D_SOD123FL
D4, D6: 1N5817WS; D_SOD323
D5: B5819WT; D_SOD523
D14: Red; LED0603
FB1, FB2: 0R/800mA; L0603
FB3, FB4: 1K/300mA; L0603
FPC2: CROWPANEL_ADVANCE_HMI_FPC-6PIN-0.5MM
J1: TYPEC-3.0-16P-SMD; USB-3.0TYPEC-SMD
J2, J12, J13: HY2.0-4P-SMT; CONNECTOR_4P-SMD-2.0
J3: PH2.0WT-2PIN
J4, J6, J7, J8: THO-M3.25MM-HOLE; THO-M3.2*5MM-HOLE
J5: HOLDER-MICROSD-9P; 9P-SMD-W/-RING
J9, J11: HEADER-7P-18.28X2.5; H7-2.54-18.28X2.5X5MM
J10: XH2.54-4P-SMT; XH2.54-4P-SMD
J14: WAFER-PH2.0-2PLB; CONN-TH_2P-P2.00_XUNPU_WAFER-PH2.0-2PLB
J15: HC-PZ200-8.7L-1X4PZ1; TEST-PIN-4-2.0MM
JP1: COOPER_0.5MM-40PIN40PIN; COOPER_0.5MM*40P
K1: DSHP02TS-S; SW-SMD_DSHP02TS-S_1
K3, K4: PB157; 157SW
L1, L2: 4.7uH/3A; L0420
L3: NC; L0603
MIC1: LMD3526B261-OFA01; MIC-SMD_5P-L3.5-W2.7-P1.67
P1, P2, P3, P4, P5, P6, P7, P8, P9, P10, P11, P12, P13, P14, P17, P18, P19, P20, P21, P22, P23, P24, P25, P26, P27, P28, P29, P31, P32, P33, P34, P35, P36, P37, P38, P39, P40, P41, P42, P43, P44, P45, P46, P47, P48, P49, P50, P51, P52, P53, P54, P55, P56, P57, P58, P59, P60, P61, P62, P63, P64, P65, P66, P67, P68, P69, P70, P71, P72, P75, P76: TEST_PADPAD-1.5MM; TEST_PAD-1.5MM
Q1, Q2: BSS138W_SOT323; MOS_SOT323
Q3, Q6, Q8, Q9: AO3401; PMOS_SOT23
Q4, Q7: SS8050W-SOT323; MOS_SOT323
Q5: BAT54C-7-F; SOT-23
R1, R2, R4, R17, R26, R32, R62, R69, R70: 5.1K; R0603-SP
R3, R37: 100K; R0603-SP
R5, R9, R15, R18, R19, R22, R27, R28, R30, R33, R35, R36, R39, R42, R51, R52, R56, R57, R59: 10K; R0603-SP
R6, R7, R8, R10, R41, R44, R45, R46, R47, R48, R49: 0R; R0603-SP
R11, R12, R13, R14, R25, R34: 4.7K; R0603-SP
R16, R31: 2K; R0603-SP
R20: 45.3K; R0603-SP
R21, R50: 1K; R0603-SP
R23: 47K; R0603-SP
R24: 3.9R; R0603-SP
R29, R58: 10K/NC; R0603-SP
R38, R43: 100R; R0603-SP
R40: 3.6R; R0603-SP
U1: CH340K; ESOP-10-EP-150MIL
U2: TP4059-SOT23-6; SOT23-6L
U3: RY3420; IC_SOT23-5
U4: PCF8563MDTR(XBLW); MSOP-8
U5: ESP32-S3-WROOM-1; ESP32-S3-WROOM-1-SMD41
U6: MT9201; COOPER_SOT23-6
U8, U11: CH486F; QFN-28_L4.0-W4.0-P0.40-BL-EP2.8
U9: UMH3NTN; SOP65P210X100-6N
U10: NS4168-ESOP-8
U13: STC8H1K28-36I-LQFP32; QFP80P900X900X165-32N
Y1: 32.768KHZ; SMD3215-2P

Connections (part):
3V3: C6.2, C7.2, C8.2, C10.2, C12.2, C14.2, C15.2, C22.2, C23.2, C24.2, C25.2, C26.2, C28.2, C47.1, D1.1, D1.2, FB1.1, FB2.1, FPC2.5, J5.4 (VDD), J9.5, J9.5-5 (5), JP1.P$37 (VCC), K1.1, K1.2, L2.2, P13.P$1, P38.P$1, P44.P$1, P61.P$1, Q1.1 (G), Q2.1 (G), Q5.1, Q8.2 (S), Q9.2 (S), R11.1, R14.1, R15.2, R20.2, R24.2, R25.2, R26.2, R27.2, R28.2, R29.2, R30.2, R34.2, R42.2, R47.2, R51.2, U8.24 (VDD), U11.24 (VDD), U13.10 (VCC/AVCC), U13.11 (ADC_VREF+)
3V3$: C2.2, U1.10 (V3)
3V3_1: C41.2, FB1.2, MIC1.4 (VDD)
3V3_NS_CTRL: R3.1, R50.1, U10.1 (CTRL)
3V3_OUT: J2.3, J12.3, J13.3, P32.P$1, P43.P$1, Q8.3 (D)
+5V_IN: D2.+, D6.+, J10.3, P17.P$1
+VBUS1: C1.2, D4.+, D10.+, J1.A4, J1.A9, J1.B4, J1.B9, P1.P$1, U1.7 (VCC)
+VC_IN: C3.2, D4.-, D6.-, Q3.1 (G), R1.2, R2.2, R17.2, R18.2, U2.4 (VCC)
DA1: J5.8 (DATA1), R15.1
DA2: J5.1 (DATA2), R30.1
DTR: R5.2, U1.4 (DTR#), U9.4 (E2)
ESP32_EN: C16.2, K4.2, R22.2, U5.3 (EN), U9.6 (C1), U13.9 (P5.4)
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
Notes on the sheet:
BOOT
RESET
HIG: SPI Boot
LOW: Download Boot
HIG: ESP32 Enable
LOW: ESP32 Off
Power
USB interface
Automatic download circuit
Battery and control
RTC clock
ESP32-S3-N16R8
5.0 inch IPS interface
Capacitive touch interface
Passive buzzer
SD card
Wireless module
UART & I2C & GPIO extensions
Indicator lights for power and charging
I2C>IO extension
DC-DC Step Down
Right channel
I2S MIC
Function switching
